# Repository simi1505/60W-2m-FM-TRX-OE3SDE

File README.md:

# 60W-2m-FM-TRX-OE3SDE
 60W 2m FM TRX with RA60H1317M1A + DRA818V by OE3SDE

## Result

**Figure 1**: Final 60W 2m FM TRX in enclosure.

**Figure 2**: 60W 2m FM TRX on air.

## 60W TRX

**Figure 3**: 3D View of RA60H1317M1A PCB.

**Figure 4**: Top View of RA60H1317M1A PCB.

## 1W TRX and control PCB

**Figure 5**: Top View of DRA818V PCB.

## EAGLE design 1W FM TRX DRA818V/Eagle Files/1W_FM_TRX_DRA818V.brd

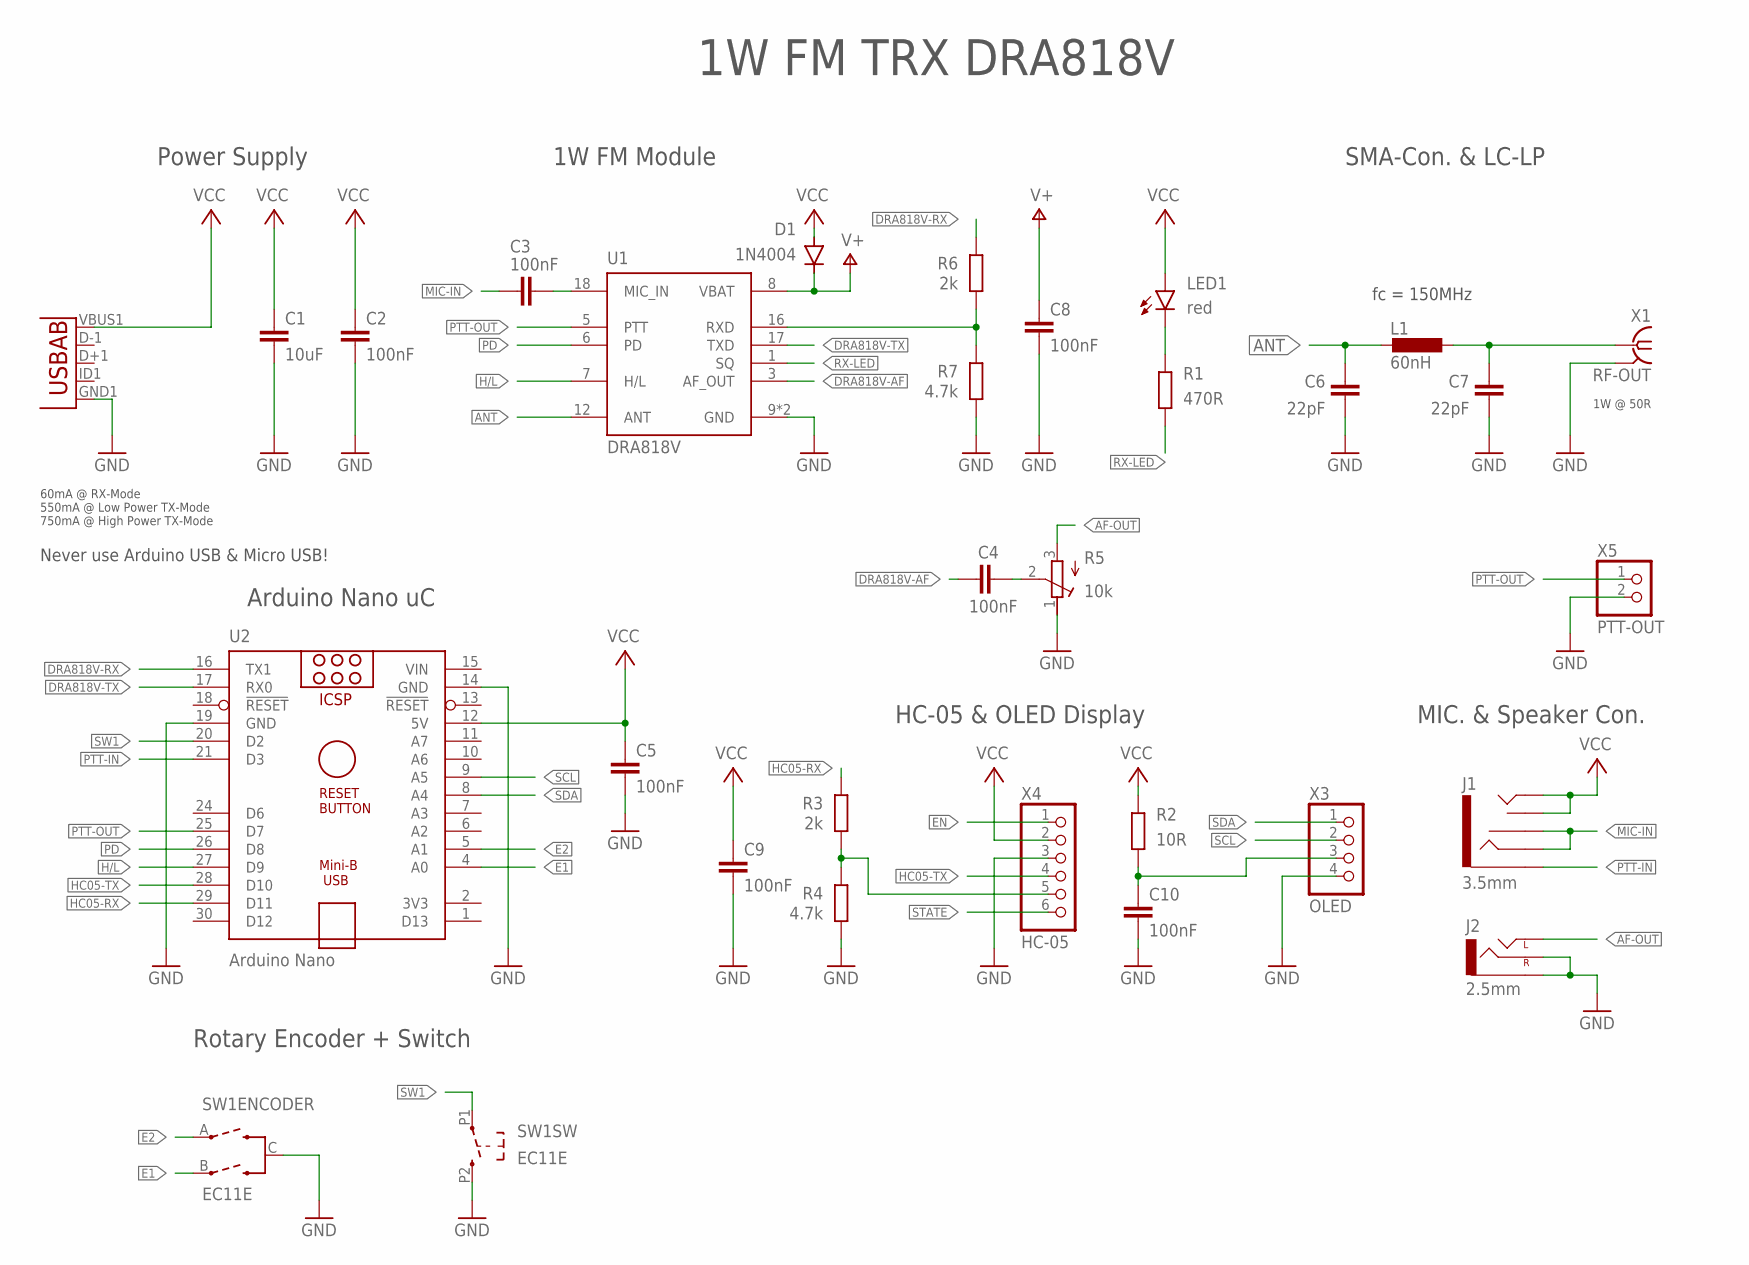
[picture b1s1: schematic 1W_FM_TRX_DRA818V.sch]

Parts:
C1: 10uF; C0805K
C2, C3, C4, C5, C8, C9, C10: 100nF; C0805K
C6, C7: 22pF; C0805K
D1: 1N4004; DO41-10
J1: 3.5mm; AUDIO-JACK
J2: 2.5mm; STEREOJACK2.5MM_STEREOJACK2.5MM
L1: 60nH; L8530M
LED1: red; CHIP-LED0805
R1: 470R; R0805
R2: 10R; R0805
R3, R6: 2k; R0805
R4, R7: 4.7k; R0805
R5: 10k; RTRIM3314J
SW1: EC11E; EC11E_INCREMENTAL_ENCODER
U1: DRA818V; DORJI_DRA818V
U2: Arduino Nano; ARDUINO_NANO
U3: USB Micro; USB-MICRO-SMD
X1: RF-OUT; J502-ND-142-0711-821/826
X3: OLED; 1X04
X4: HC-05; 1X06
X5: PTT-OUT; 1X02

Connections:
AF-OUT: J2.SHIELD (LEFT), R5.3 (A)
ANT: C6.2, L1.2, U1.12 (ANT)
DRA818V-AF: C4.1, U1.3 (AF_OUT)
DRA818V-RX: R6.2, U2.16 (TX1)
DRA818V-TX: U1.17 (TXD), U2.17 (RX0)
E1: SW1.B, U2.4 (A0)
E2: SW1.A, U2.5 (A1)
EN: X4.1
GND: C1.2, C2.2, C5.2, C6.1, C7.1, C8.1, C9.2, C10.2, J2.RING1 (SLEEVE), J2.TIP (RIGHT), R4.1, R5.1 (E), R7.1, SW1.C, SW1.P2 (2), U1.9 (GND), U1.10 (GND), U2.14 (GND), U2.19 (GND), U3.GND1 (GND), X1.G@1 (GND), X1.G@2 (GND), X1.G@3 (GND), X1.G@4 (GND), X3.4, X4.3, X5.2
H/L: U1.7 (H/L), U2.27 (D9)
HC05-RX: R3.2, U2.29 (D11)
HC05-TX: U2.28 (D10), X4.4
MIC-IN: C3.1, J1.RING, J1.RSH
unnamed: C3.2, U1.18 (MIC_IN)
unnamed: R3.1, R4.2, X4.5
unnamed: LED1.C, R1.2
unnamed: C4.2, R5.2 (S)
unnamed: C7.2, L1.1, X1.1 (RF)
unnamed: C10.1, R2.1, X3.3
unnamed: R6.1, R7.2, U1.16 (RXD)
PD: U1.6 (PD), U2.26 (D8)
PTT-IN: J1.SLEEVE, U2.21 (D3)
PTT-OUT: U1.5 (PTT), U2.25 (D7), X5.1
RX-LED: R1.1, U1.1 (SQ)
SCL: U2.9 (A5), X3.2
SDA: U2.8 (A4), X3.1
STATE: X4.6
SW1: SW1.P1 (1), U2.20 (D2)
V+: C8.2, D1.C, U1.8 (VBAT)
VCC: C1.1, C2.1, C5.1, C9.1, D1.A, J1.TIP, J1.TSH, LED1.A, R2.2, U2.12 (5V), U3.VBUS1 (VBUS), X4.2
VIN: U2.15 (VIN)

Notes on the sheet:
1W FM TRX DRA818V
60mA @ RX-Mode 550mA @ Low Power TX-Mode 750mA @ High Power TX-Mode
1W @ 50R
1W FM Module
Arduino Nano uC
Power Supply
SMA-Con. & LC-LP
HC-05 & OLED Display
MIC. & Speaker Con.
Rotary Encoder + Switch
fc = 150MHz
Never use Arduino USB & Micro USB!

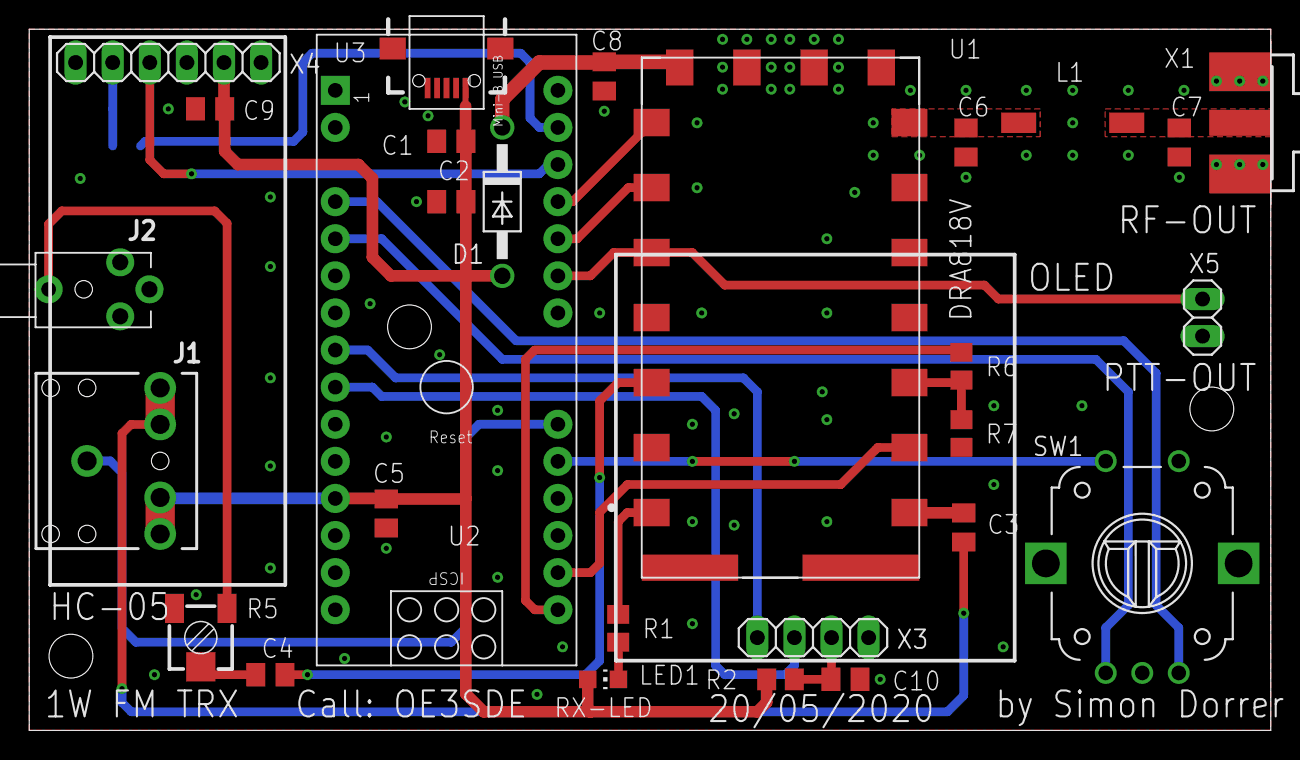
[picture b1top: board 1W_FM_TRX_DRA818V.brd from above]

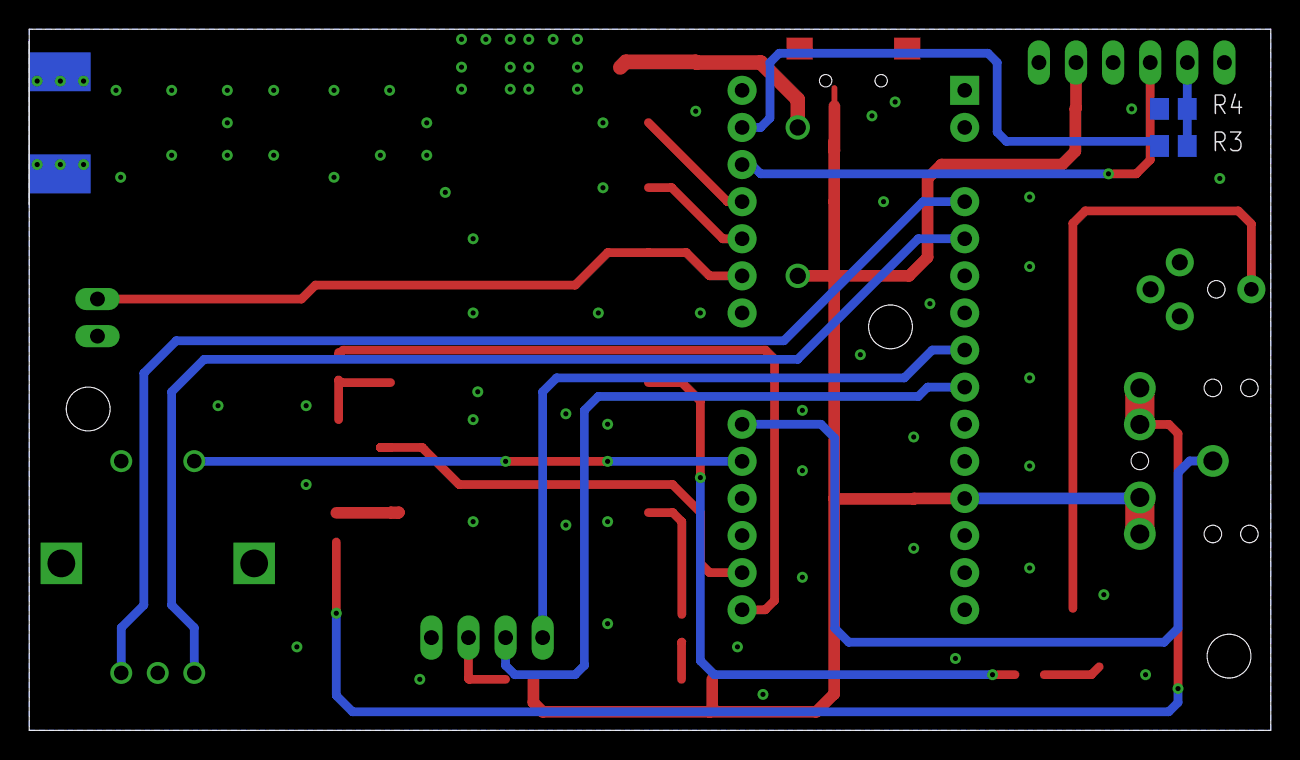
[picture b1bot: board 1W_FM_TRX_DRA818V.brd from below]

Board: 2 copper layers, 85.0 x 48.0 mm, 30 parts (2 on the bottom side), 28 nets.

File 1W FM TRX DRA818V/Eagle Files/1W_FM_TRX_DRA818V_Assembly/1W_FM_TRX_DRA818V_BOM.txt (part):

Partlist exported from E:/Simon Dorrer/DIY Projekte/Amateurfunkprojekte/DIY KITs/VHF/1W FM TRX DRA818V/Eagle Files/1W FM TRX DRA818V.sch at 24/02/2021 19:53

Qty Value        Device                      Package                         Parts                       Description                                                                                                   AVAILABILITY DESCRIPTION MF                 MP      MPN          OC_FARNELL OC_NEWARK PACKAGE                POPULARITY PRICE PROD_ID    SF_ID     SPICEMODEL SPICEPREFIX SPICEPREFIXL
7   100nF        C-EUC0805K                  C0805K                          C2, C3, C4, C5, C8, C9, C10 CAPACITOR, European symbol                                                                                                                                                                                                 52                                               C                       
1   10R          R-EU_R0805                  R0805                           R2                          RESISTOR, European symbol                                                                                                                                                                                                  86                                               R                       
1   10k          R-TRIMM3314J                RTRIM3314J                      R5                          Trimm resistor                                                                                                                                                                                                             0                                     X                      POT         
1   10uF         C-EUC0805K                  C0805K                          C1                          CAPACITOR, European symbol                                                                                                                                                                                                 52                                               C                       
1   1N4004       1N4004                      DO41-10                         D1                          DIODE                                                                                                                                                                                                                      82                                                                       
1   2.5mm        AUDIO_JACK_2.5MM_2.5MM      STEREOJACK2.5MM_STEREOJACK2.5MM J2                          Audio Jack                                                                                                                                                                                                                                  CONN-09878                                              
2   22pF         C-EUC0805K                  C0805K                          C6, C7                      CAPACITOR, European symbol                                                                                                                                                                                                 52                                               C                       
2   2k           R-EU_R0805                  R0805                           R3, R6                      RESISTOR, European symbol                                                                                                                                                                                                  86                                               R                       
1   3.5mm        AUDIO_JACK_3.5MM_PTH        AUDIO-JACK                      J1                          Audio Jack                                                                                                                                                                                                                                  CONN-08774 PRT-08032                                    
2   4.7k         R-EU_R0805                  R0805                           R4, R7                      RESISTOR, European symbol                                                                                                                                                                                                  86                                               R                       
1   470R         R-EU_R0805                  R0805                           R1                          RESISTOR, European symbol                                                                                                                                                                                                  86                                               R                       
1   60nH         L-EUL8530M                  L8530M                          L1                          INDUCTOR, European symbol                                                                                                                                                                                                  0                                                L                       
1   Arduino Nano ARDUINO_NANO                ARDUINO_NANO                    U2                          Arduino Nano V3.0                                                                                                                                                                                                                                                                                   
1   DRA818V      DRA818V                     DORJI_DRA818V                   U1                          VHF Band Voice Transceiver Module                                                                             Unavailable              DORJI              DRA818V                                   Package Analog Devices            None                                                          
1   EC11E        ENCODER_SW1-PEC12           EC11E_INCREMENTAL_ENCODER       SW1                         Incremental Encoder with push switch                                                                                                                                                                                                                                                                
1   HC-05        PINHD-1X6                   1X06                            X4                          PIN HEADER                                                                                                                                                                                                                                                                                          
1   OLED         PINHD-1X4                   1X04                            X3                          PIN HEADER                                                                                                                                                                                                                                                                                          
1   PTT-OUT      PINHD-1X2                   1X02                            X5                          PIN HEADER                                                                                                                                                                                                                                                                                          
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
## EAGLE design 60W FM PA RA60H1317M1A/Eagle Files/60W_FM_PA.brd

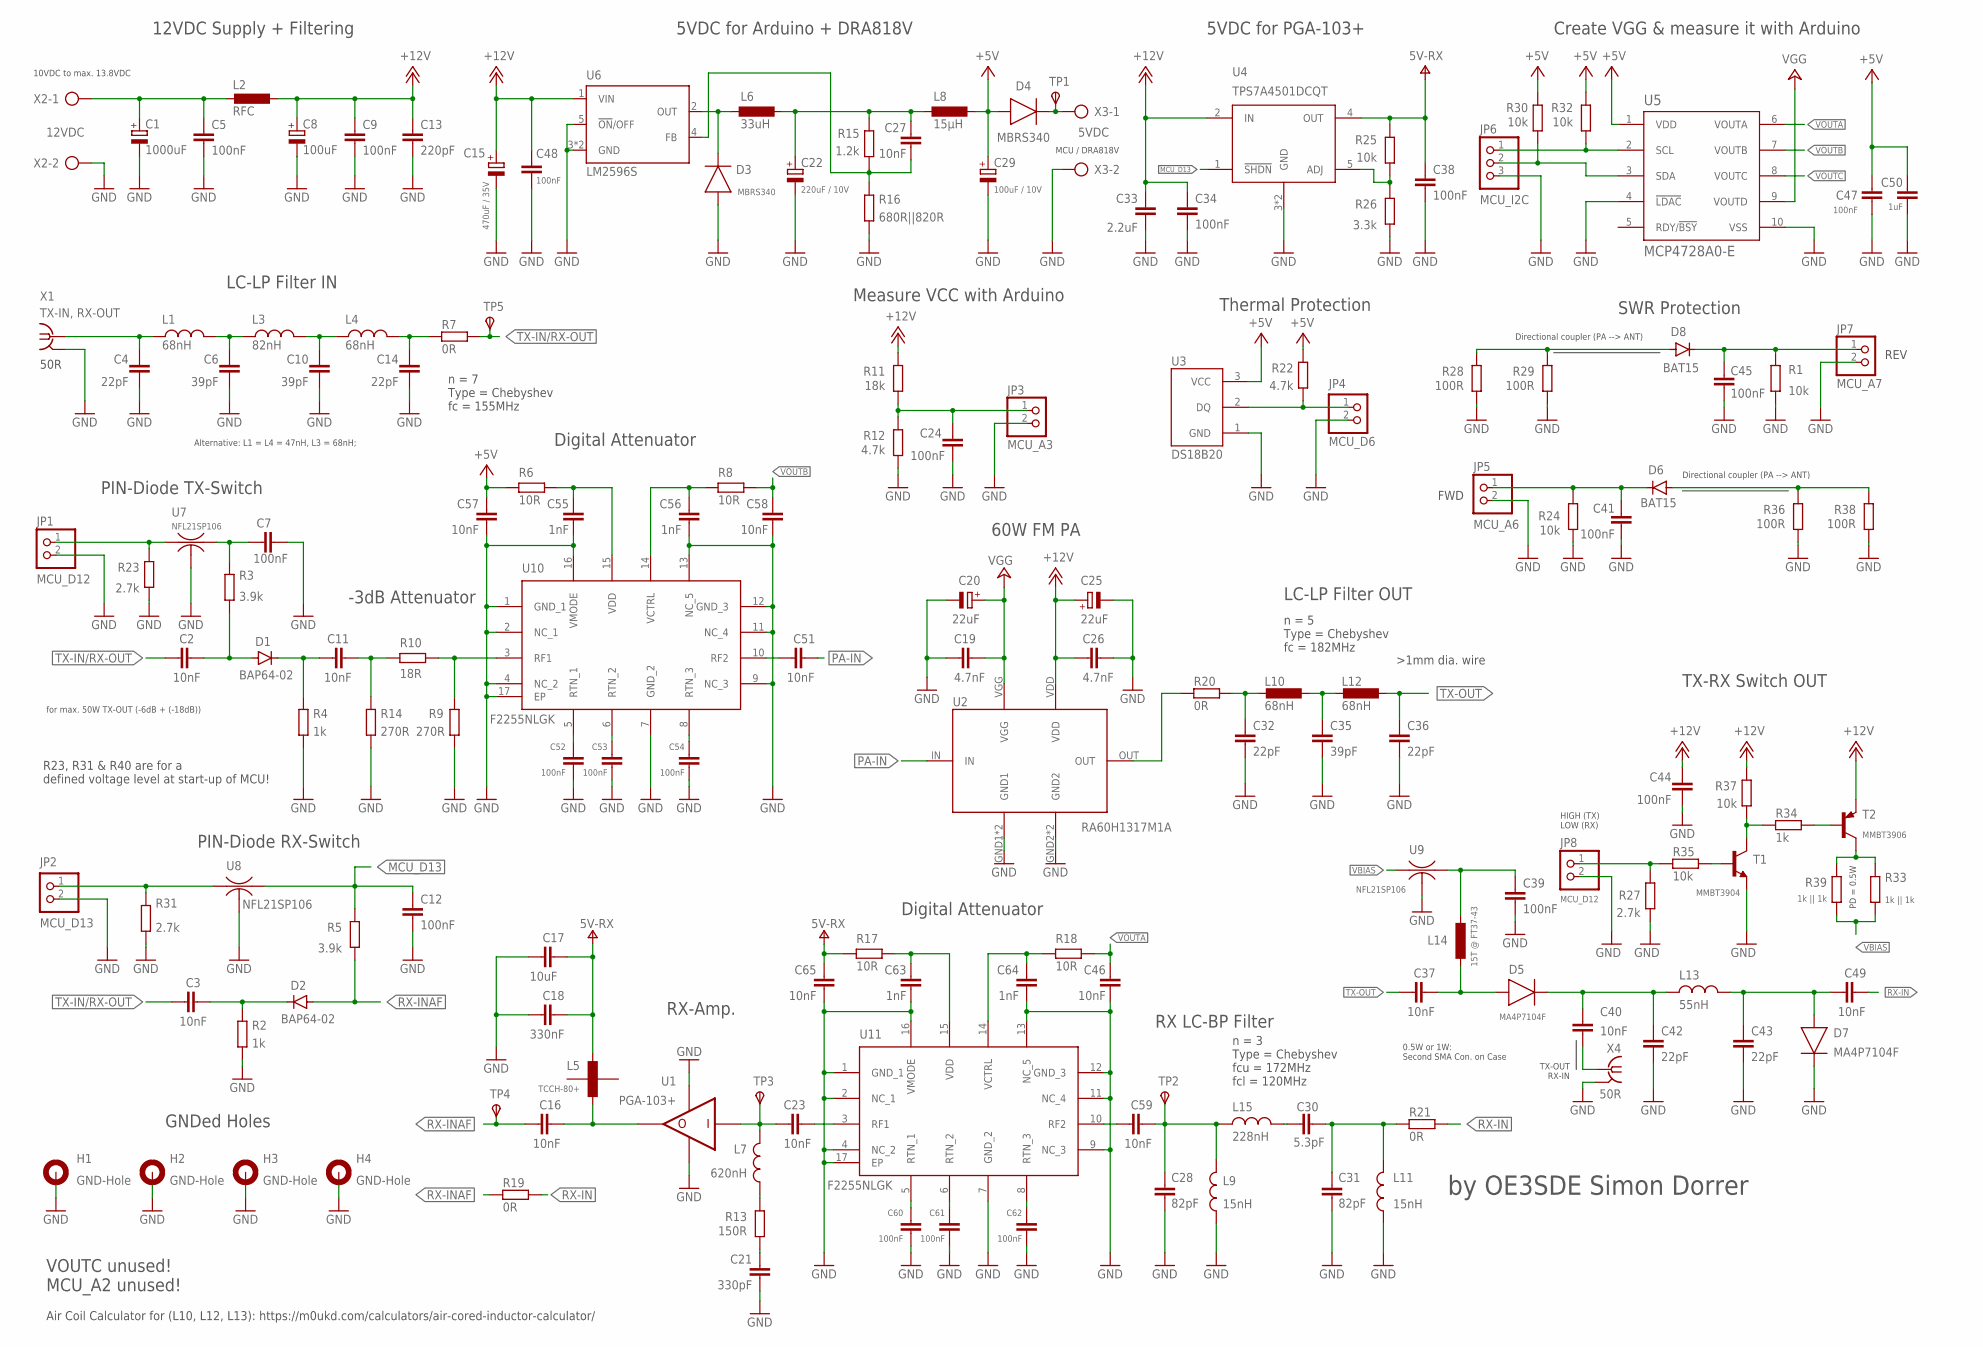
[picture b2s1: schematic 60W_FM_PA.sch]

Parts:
C1: 1000uF; CAPAE1030X1050N
C2, C3, C11, C16, C23, C27, C46, C51, C57, C58, C59, C65: 10nF; CAPC2012X110
C4, C14: 22pF; CAPC2012X110
C5, C7, C9, C12, C24, C34, C38, C39, C41, C44, C45, C47, C48: 100nF; CAPC2012X110
C6, C10: 39pF; CAPC2012X110
C8: 100uF; CAPAE1030X1050N
C13: 220pF; CAPC2012X110
C15: 470uF / 35V; CAPAE1030X1050N
C17: 10uF; CAPC2012X110
C18: 330nF; CAPC2012X110
C19, C26: 4.7nF; CAPC2012X110
C20, C25: 22uF; SMC_D
C21: 330pF; CAPC2012X110
C22: 220uF / 10V; CAPMP7343X310N
C28, C31: 82pF; CAPC2012X110
C29: 100uF / 10V; CAPMP7343X310N
C30: 5.3pF; CAPC2012X110
C32, C36, C42, C43: 22pF; CAPC3216X135
C33: 2.2uF; CAPC2012X110
C35: 39pF; CAPC3216X135
C37, C40, C49: 10nF; CAPC3216X135
C50: 1uF; CAPC2012X110
C52, C53, C54, C60, C61, C62: 100nF; CAPC1608X85
C55, C56, C63, C64: 1nF; CAPC2012X110
D1, D2: BAP64-02; SOD523
D3, D4: MBRS340; DIOM7959X625N
D5, D7: MA4P7104F; SODFL5336X110
D6, D8: BAT15; SOD-323
H1, H2, H3, H4: GND-Hole; 3,0-PAD
JP1, JP8: MCU_D12; 1X02
JP2: MCU_D13; 1X02
JP3: MCU_A3; 1X02
JP4: MCU_D6; 1X02
JP5: MCU_A6; 1X02
JP6: MCU_I2C; 1X03
JP7: MCU_A7; 1X02
L1, L4: 68nH; INDC2009X120
L2: RFC; T50-6SMD
L3: 82nH; INDC2009X120
L5: TCCH-80+; TCCH-80
L6: 33uH; 1260
L7: 620nH; INDC2009X120
L8: 15µH; 1260
L9, L11: 15nH; INDC3216X190
L10, L12: 68nH; AIR-COIL-SMD
L13: 55nH; INDC3216X190
L14: 15T @ FT37-43; AIR-COIL-SMD
L15: 228nH; INDC3216X190
R1, R24, R25, R30, R32, R35, R37: 10k; RESC2012X65
R2, R4, R34: 1k; RESC2012X65
R3, R5: 3.9k; RESC2012X65
R6, R8, R17, R18: 10R; RESC2012X65
R7, R19, R21: 0R; RESC2012X65
R9, R14: 270R; RESC2012X65
R10: 18R; RESC2012X65
R11: 18k; RESC2012X65
R12, R22: 4.7k; RESC2012X65
R13: 150R; RESC2012X65
R15: 1.2k; RESC2012X65
R16: 680R||820R; RESC2012X65
R20: 0R; RESC3216X70
R23, R27, R31: 2.7k; RESC2012X65
R26: 3.3k; RESC2012X65
R28, R29, R36, R38: 100R; RESC2012X65
R33, R39: 1k || 1k; RESC2012X65
T1: MMBT3904; SOT23-BEC
T2: MMBT3906; SOT23-BEC
TP1, TP2, TP3, TP4, TP5: TPSTP10SQ; TP10SQ
U1: PGA-103+; SOT89
U2: RA60H1317M1A
U3: DS18B20; 21-0248A_MXM
U4: TPS7A4501DCQT; DCQ6
U5: MCP4728A0-E; MSOP10_MC_MCH-M
U6: LM2596S; TO263-5
U7, U8, U9: NFL21SP106; NFM21C
U10, U11: F2255NLGK; QFN50P300X300X100-17N
X1: TX-IN, RX-OUT; J502-ND-142-0711-821/826
X2: 12VDC; AK300/2
X3: 5VDC; AK300/2
X4: 50R; J502-ND-142-0711-821/826

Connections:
+5V: C29.1 (+), C47.2, C50.2, C57.1, D4.2 (A), L8.- (2), R6.1, R22.2, R30.1, R32.1, U3.3 (VCC), U5.1 (VDD)
+12V: C8.1 (+), C9.2, C13.2, C15.1 (+), C25.+, C26.1, C33.2, C34.2, C44.2, C48.2, L2.P$2 (2), R11.2, R37.1, T2.E, U2.VDD, U4.2 (IN), U6.1 (VIN)
+24V: C19.2, C20.+, U2.VGG, U5.9 (VOUTD)
D12: JP1.1, R23.1, U7.1
GND: C1.2 (-), C4.2, C5.1, C6.2, C7.1, C8.2 (-), C9.1, C10.2, C12.1, C13.1, C14.2, C15.2 (-), C17.2, C18.2, C19.1, C20.-, C21.1, C22.2 (-), C24.1, C25.-, C26.2, C28.2, C29.2 (-), C31.2, C32.2, C33.1, C34.1, C35.2, C36.2, C38.1, C39.1, C41.2, C42.2, C43.2, C44.1, C45.2, C46.2, C47.1, C48.1, C50.1, C52.2, C53.2, C54.2, C55.2, C56.2, C57.2, C58.2, C60.2, C61.2, C62.2, C63.2, C64.2, C65.2, D3.2 (A), D7.1 (C), H1.B3,0, H2.B3,0, H3.B3,0, H4.B3,0, JP1.2, JP2.2, JP3.2, JP4.2, JP5.2, JP6.3, JP7.2, JP8.2, L9.1, L11.1, R1.2, R2.2, R4.2, R9.2, R12.1, R14.2, R16.1, R23.2, R24.1, R26.2, R27.2, R28.1, R29.1, R31.2, R36.1, R38.1, T1.E, U1.2 (GND1), U1.2@1 (GND2), U2.GND1, U2.GND2, U2.GND3 (GND1), U2.GND4 (GND2), U3.1 (GND), U4.3 (GND), U4.6 (GND), U5.4 (!LDAC), U5.10 (VSS), U6.3 (GND), U6.5 (!ON!/OFF), U6.6 (GND), U7.2@1 (2), U7.2@2 (2), U8.2@1 (2), U8.2@2 (2), U9.2@1 (2), U9.2@2 (2), U10.1 (GND_1), U10.2 (NC_1), U10.4 (NC_2), U10.7 (GND_2), U10.9 (NC_3), U10.11 (NC_4), U10.12 (GND_3), U10.13 (NC_5), U10.16 (VMODE), U10.17 (EP), U11.1 (GND_1), U11.2 (NC_1), U11.4 (NC_2), U11.7 (GND_2), U11.9 (NC_3), U11.11 (NC_4), U11.12 (GND_3), U11.13 (NC_5), U11.16 (VMODE), U11.17 (EP), X1.G@1 (2), X1.G@2 (2), X1.G@3 (2), X1.G@4 (2), X2.2, X3.2, X4.G@1 (2), X4.G@2 (2), X4.G@3 (2), X4.G@4 (2)
MCU_D13: C12.2, R5.1, U4.1 (!SHDN), U8.3
unnamed: C23.2, L7.2, TP3.TP, U1.1 (IN)
unnamed: C16.1, L5.RF-DC, U1.3 (OUT)
unnamed: JP8.1, R27.1, R35.2
unnamed: C6.1, L1.2, L3.1
unnamed: C10.1, L3.2, L4.1
unnamed: C24.2, JP3.1, R11.1, R12.2
unnamed: C59.2, U11.10 (RF2)
unnamed: L7.1, R13.2
unnamed: C21.2, R13.1
unnamed: C3.1, D2.C, R2.1
unnamed: C23.1, U11.3 (RF1)
unnamed: C1.1 (+), C5.2, L2.P$1 (1), X2.1
unnamed: JP6.1, R32.2, U5.2 (SCL)
unnamed: C14.1, L4.2, R7.2
unnamed: JP6.2, R30.2, U5.3 (SDA)
unnamed: JP2.1, R31.1, U8.1
unnamed: R25.2, R26.1, U4.5 (ADJ)
unnamed: C32.1, L10.P$1 (1), R20.1
unnamed: C35.1, L10.P$2 (2), L12.P$1 (1)
unnamed: C43.1, C49.2, D7.2 (A), L13.2
unnamed: C40.1, C42.1, D5.1 (C), L13.1
unnamed: C28.1, C59.1, L9.2, L15.1, TP2.TP
unnamed: C30.2, C31.1, L11.2, R21.2
unnamed: D4.1 (C), TP1.TP, X3.1
unnamed: R20.2, U2.OUT
unnamed: C51.2, U10.10 (RF2)
unnamed: JP4.1, R22.1, U3.2 (DQ)
unnamed: C52.1, U10.5 (RTN_1)
unnamed: C41.1, D6.C, JP5.1, R24.2
unnamed: C45.1, D8.C, JP7.1, R1.1
unnamed: D8.A, R28.2, R29.2
unnamed: C37.1, D5.2 (A), L14.P$1 (1)
unnamed: R34.2, R37.2, T1.C
unnamed: C53.1, U10.6 (RTN_2)
unnamed: D3.1 (C), L6.+ (1), U6.2 (OUT)
unnamed: C22.1 (+), C27.2, L6.- (2), L8.+ (1), R15.2
unnamed: C2.1, D1.A, R3.2
unnamed: R34.1, T2.B
unnamed: C11.2, D1.C, R4.1
unnamed: R35.1, T1.B
unnamed: D6.A, R36.2, R38.2
unnamed: C54.1, U10.8 (RTN_3)
unnamed: C27.1, R15.1, R16.2, U6.4 (FB)
unnamed: C55.1, R6.2, U10.15 (VDD)
unnamed: C56.1, R8.1, U10.14 (VCTRL)
unnamed: C11.1, R10.1, R14.1
unnamed: C60.1, U11.5 (RTN_1)
unnamed: C61.1, U11.6 (RTN_2)
unnamed: C62.1, U11.8 (RTN_3)
unnamed: C63.1, R17.2, U11.15 (VDD)
unnamed: C64.1, R18.1, U11.14 (VCTRL)
unnamed: R9.1, R10.2, U10.3 (RF1)
unnamed: R33.1, R39.1, T2.C
unnamed: C7.2, R3.1, U7.3
unnamed: C30.1, L15.2
unnamed: C39.2, L14.P$2 (2), U9.3
unnamed: C40.2, X4.1
PA-IN: C51.1, U2.IN
RX-IN: C49.1, R19.1, R21.1
RX-INAF: C16.2, D2.A, R5.2, R19.2, TP4.TP
RX-OUT: C4.1, L1.1, X1.1
TX-IN/RX-OUT: C2.2, C3.2, R7.1, TP5.TP
TX-OUT: C36.1, C37.2, L12.P$2 (2)
V+: C17.1, C18.1, C38.2, C65.1, L5.DC, R17.1, R25.1, U4.4 (OUT)
VBIAS: R33.2, R39.2, U9.1
VOUTA: C46.1, R18.2, U5.6 (VOUTA)
VOUTB: C58.1, R8.2, U5.7 (VOUTB)
VOUTC: U5.8 (VOUTC)

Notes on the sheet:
GNDed Holes
RX-Amp.
RX LC-BP Filter
n = 3 Type = Chebyshev fcu = 172MHz fcl = 120MHz
LC-LP Filter IN
60W FM PA
12VDC Supply + Filtering
5VDC for Arduino + DRA818V
n = 7 Type = Chebyshev fc = 155MHz
Measure VCC with Arduino
10VDC to max. 13.8VDC
Create VGG & measure it with Arduino
5VDC for PGA-103+
PIN-Diode RX-Switch
TX-RX Switch OUT
n = 5 Type = Chebyshev fc = 182MHz
LC-LP Filter OUT
Digital Attenuator
-3dB Attenuator
for max. 50W TX-OUT (-6dB + (-18dB))
PIN-Diode TX-Switch
50R
TX-OUT RX-IN
0.5W or 1W: Second SMA Con. on Case
Thermal Protection
SWR Protection
by OE3SDE Simon Dorrer
Directional coupler (PA --> ANT)
MCU / DRA818V
REV
FWD
VOUTC unused! MCU_A2 unused!
HIGH (TX) LOW (RX)
R23, R31 & R40 are for a defined voltage level at start-up of MCU!
Alternative: L1 = L4 = 47nH, L3 = 68nH;
PD = 0.5W
Air Coil Calculator for (L10, L12, L13): https://m0ukd.com/calculators/air-cored-inductor-calculator/

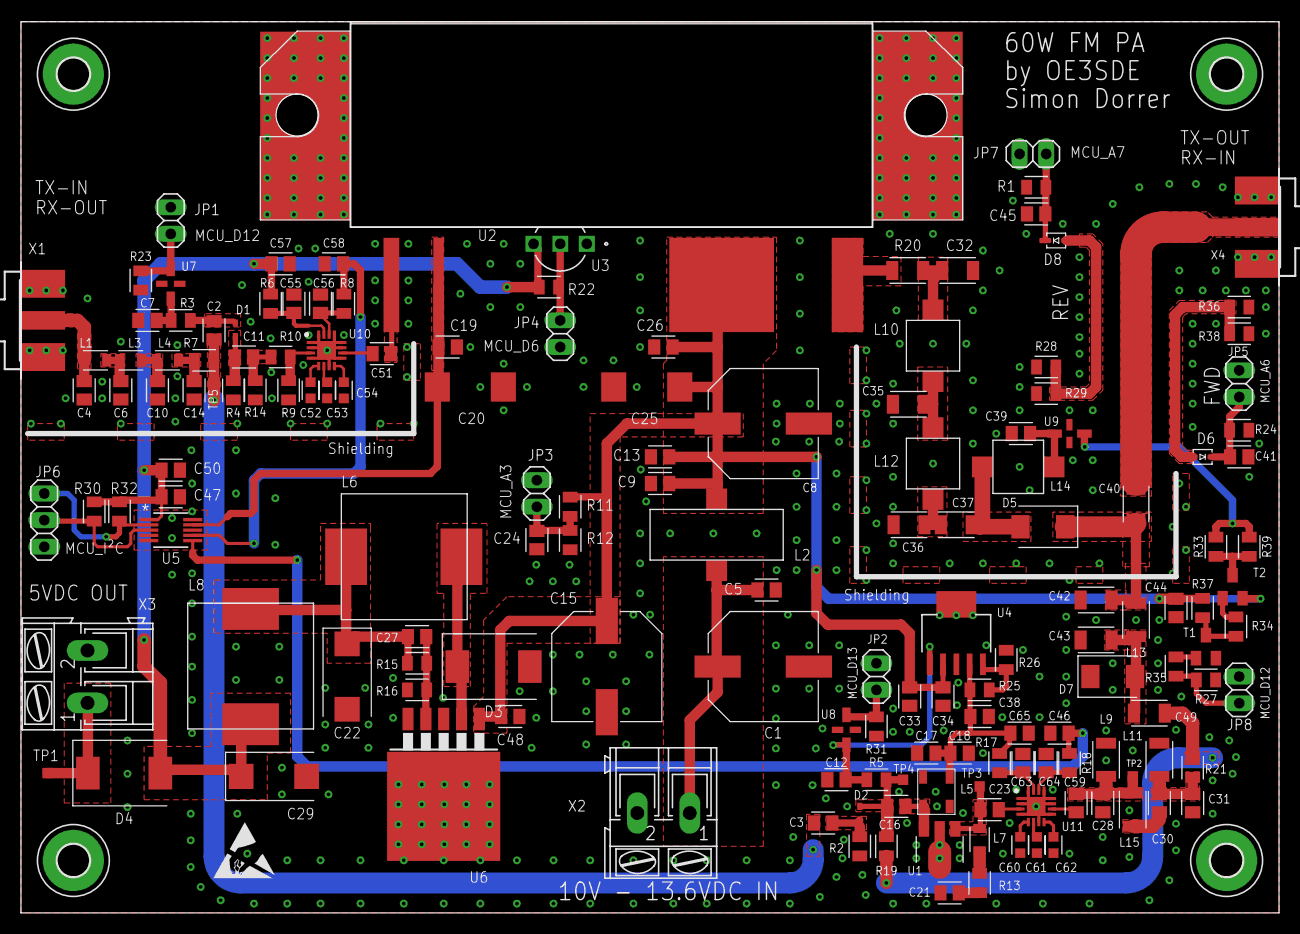
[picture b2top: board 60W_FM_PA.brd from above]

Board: 2 copper layers, 120.0 x 85.0 mm, 161 parts (0 on the bottom side), 73 nets.

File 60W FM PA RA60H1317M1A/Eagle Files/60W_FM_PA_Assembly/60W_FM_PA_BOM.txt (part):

Partlist exported from D:/Simon Dorrer/DIY Projekte/Amateurfunkprojekte/DIY KITs/VHF/60W FM PA RA60H1317M1A/Eagle/60W FM PA.sch at 15/04/2021 13:50

Qty Value         Device                           Package                  Parts                                                        Description                                                             BUILT_BY    CATEGORY  COPYRIGHT                                                   CREATED_BY    CURRENT_RATING DATASHEET_URL                       DESCRIPTION                                           DIGIKEY_PART_NUMBER FAMILY_NAME        FORWARD_CURRENT GENERIC_PART_NUMBER HEIGHT INDUSTRY_STD_PKG_TYPE MANUFACTURER        MANUFACTURER_NAME MANUFACTURER_PART_NUMBER MF                     MOUSER_PART_NUMBER MOUSER_PRICE-STOCK                                              MPN              OC_FARNELL OC_NEWARK OPERATING_TEMP PACKAGE PACKAGE_DESIGNATOR PART_STATUS PIN_COUNT POPULARITY RATING REVERSE_VOLTAGE REVISION ROHS_COMPLIANT SERIES SOURCELIBRARY           SPICEPREFIX SUB-CATEGORY THERMALLOSS TOLERANCE TP_SIGNAL_NAME TYPE VALUE VENDOR                    VOLTAGE_RATING
3   0R            R_CHIP-0805(2012-METRIC)         RESC2012X65              R7, R19, R21                                                 Resistor Fixed - Generic                                                            Resistor                                                                                                                                                                                                                                                                                                                                                                                                                                                                                                                                                                                                                                                                                 Fixed                                                                                                
1   0R            R_CHIP-1206(3216-METRIC)         RESC3216X70              R20                                                          Resistor Fixed - Generic                                                            Resistor                                                                                                                                                                                                                                                                                                                                                                                                                                                                                                                                                                                                                                                                                 Fixed                                                                                                
1   1.2k          R_CHIP-0805(2012-METRIC)         RESC2012X65              R15                                                          Resistor Fixed - Generic                                                            Resistor                                                                                                                                                                                                                                                                                                                                                                                                                                                                                                                                                                                                                                                                                 Fixed                                                                                                
1   1000uF        C-POL_ECAP-10.5MM                CAPAE1030X1050N          C1                                                           Capacitor Polarised - Generic                                                       Capacitor                                                                                                                                                                                                                                                                                                                                                                                                                                                                                                                                                                                                                                                                                                                                                                                     
4   100R          R_CHIP-0805(2012-METRIC)         RESC2012X65              R28, R29, R36, R38                                           Resistor Fixed - Generic                                                            Resistor                                                                                                                                                                                                                                                                                                                                                                                                                                                                                                                                                                                                                                                                                 Fixed                                                                                                
6   100nF         C_CHIP-0603(1608-METRIC)         CAPC1608X85              C52, C53, C54, C60, C61, C62                                 Capacitor - Generic                                                                 Capacitor                                                                                                                                                                                                                                                                                                                                                                                                                                                                                                                                                                                                                                                                                                                                                                                     
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

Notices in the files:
parts and their libraries:
SparkFun-Connectors: Licensing: Creative Commons ShareAlike 4.0 International - https://creativecommons.org/licenses/by-sa/4.0
COPYRIGHT: Copyright (C) 2018 Accelerated Designs. All rights reserved
